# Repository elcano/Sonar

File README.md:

# Sonar
Range data from an array of ultra-sonic sensors

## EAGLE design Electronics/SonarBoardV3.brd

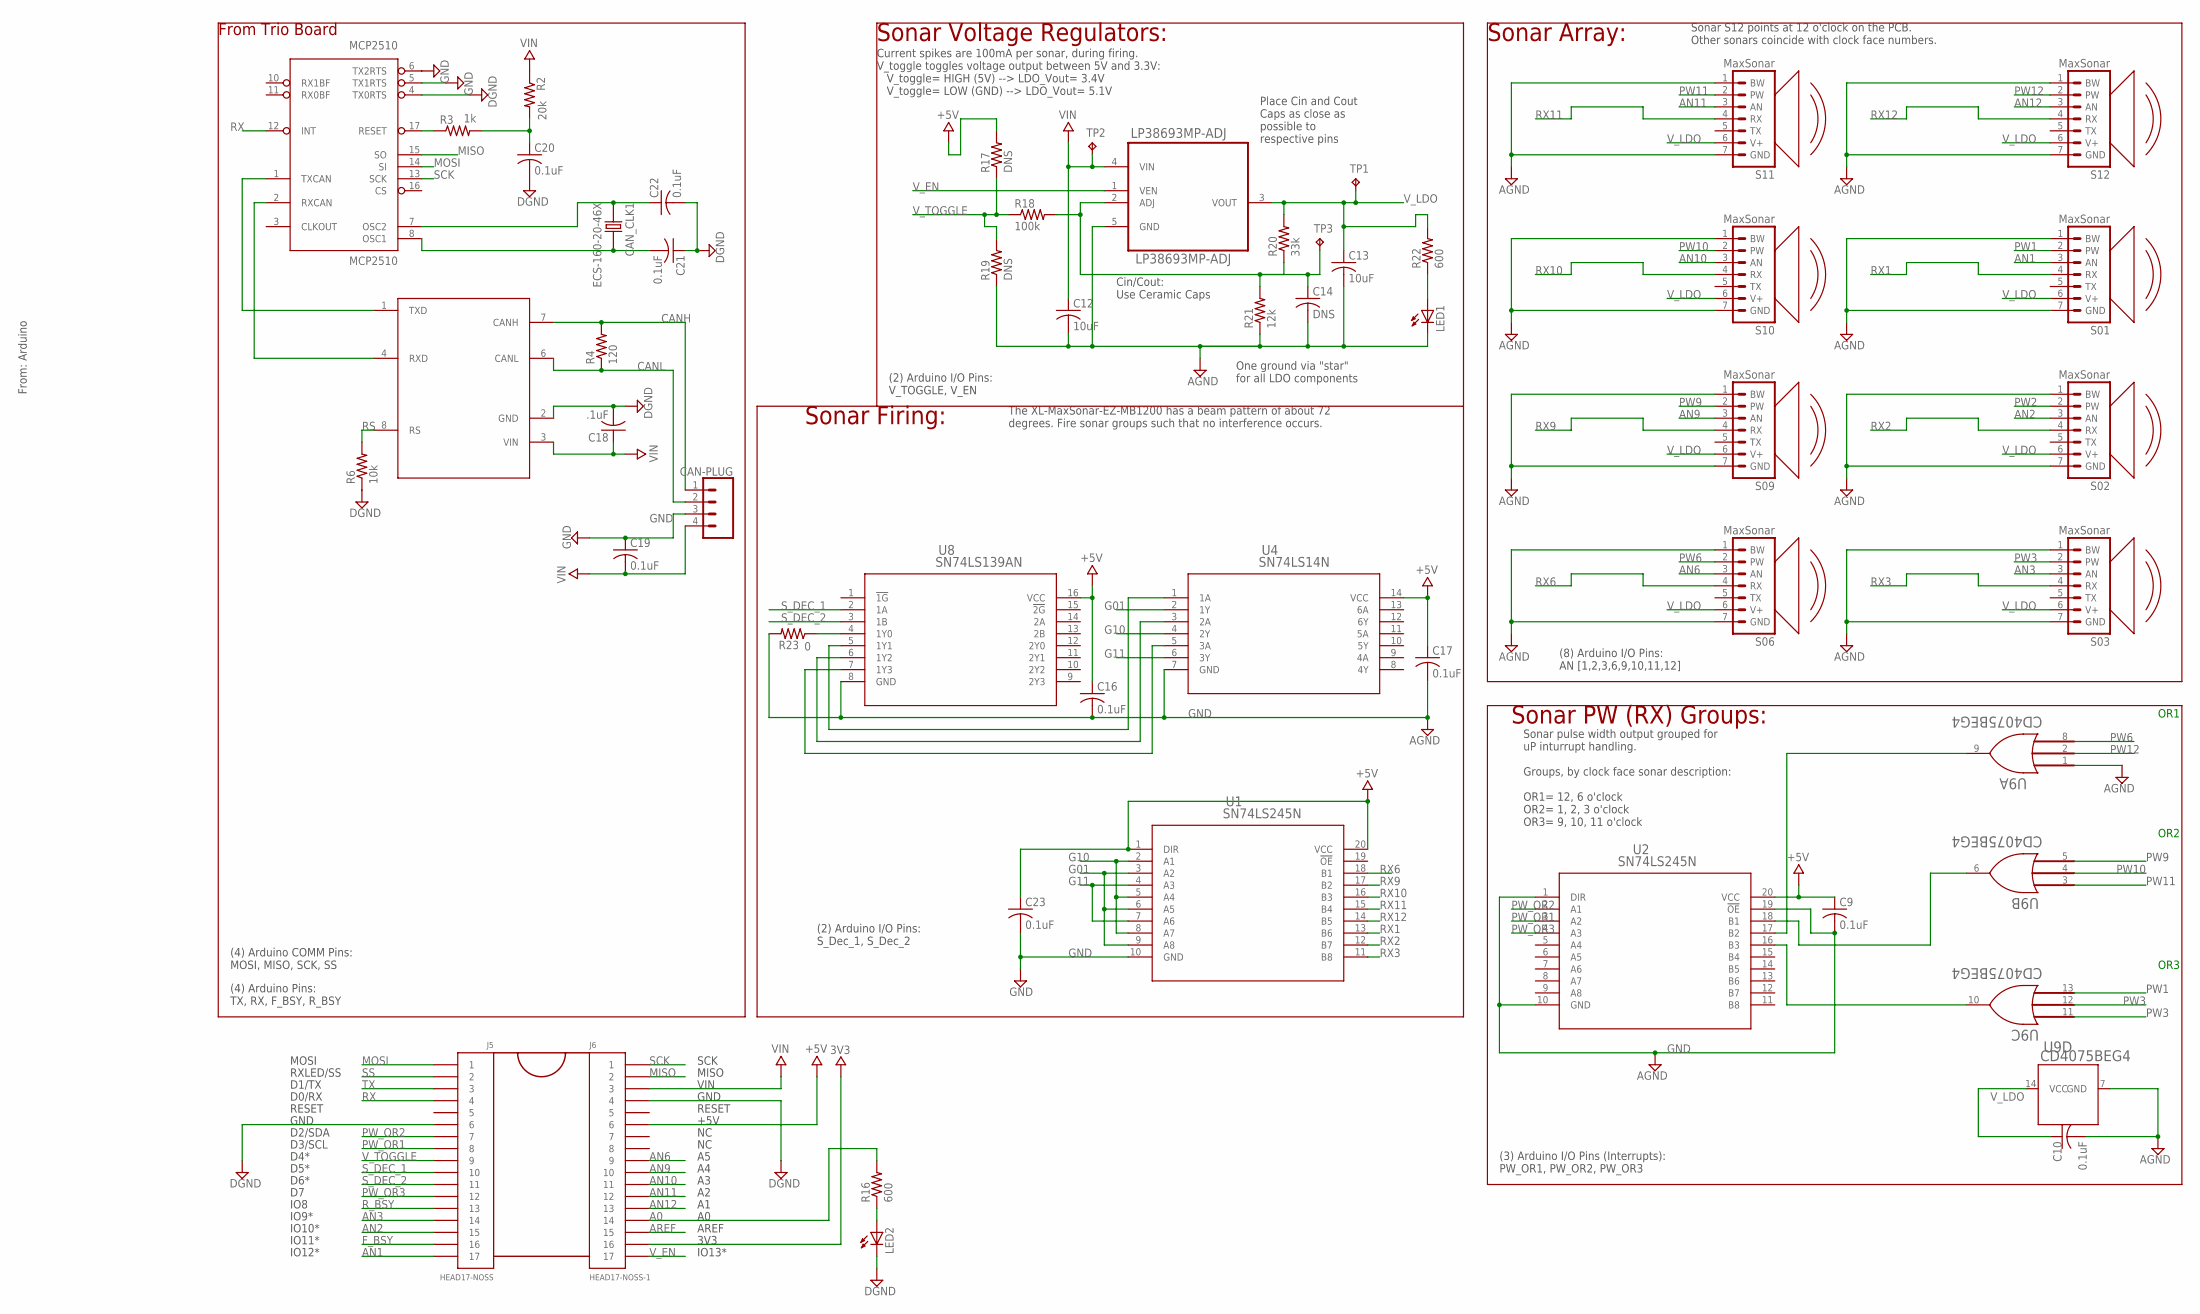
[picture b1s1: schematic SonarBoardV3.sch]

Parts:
C9, C10, C16, C17, C19, C20, C21, C22, C23: 0.1uF; C025-024X044
C12, C13: 10uF; C025-024X044
C14: DNS; C025-024X044
C18: .1uF; C025-024X044
CAN_CLK1: ECS-160-20-46X; XTAL_ECS-160-20-46X
J2: CAN-PLUG; SCREWTERMINAL-3.5MM-4
J5: HEAD17-NOSS
J6: HEAD17-NOSS-1
LED1, LED2: LED3MM
LP38693MP-ADJ: LP38693MP-ADJ; SOT150P696X180-5N
MCP2510: MCP2510; DIL18
MCP2551: MCP2551; DIL08
R2: 20k; 0207/9
R3: 1k; 0207/9
R4: 120; 0207/9
R6: 10k; 0207/9
R16, R22: 600; 0207/9
R17, R19: DNS; 0207/9
R18: 100k; 0207/9
R20: 33k; 0207/9
R21: 12k; 0207/9
R23: 0; 0207/9
S01, S02, S03, S06, S09, S10, S11, S12: MaxSonar; XL-MAXSONAR-PACKAGE
TP1, TP2, TP3: TPPAD1-17; P1-17
U1, U2: SN74LS245N; N20
U4: SN74LS14N; N14
U8: SN74LS139AN; N16
U9: CD4075BEG4; N14

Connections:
3V3: J6.16
+5V: C9.1, C16.1, C17.1, C23.1, J6.6, R17.2, U1.1 (DIR), U1.20 (VCC), U2.20 (VCC), U4.14 (VCC), U8.16 (VCC)
A0: J6.14, R16.2
AN1: J5.17, S01.3 (AN)
AN2: J5.15, S02.3 (AN)
AN3: J5.14, S03.3 (AN)
AN6: J6.9, S06.3 (AN)
AN9: J6.10, S09.3 (AN)
AN10: J6.11, S10.3 (AN)
AN11: J6.12, S11.3 (AN)
AN12: J6.13, S12.3 (AN)
AREF: J6.15
CANH: J2.1, MCP2551.7 (CANH), R4.2
CANL: J2.2, MCP2551.6 (CANL), R4.1
F_BSY: J5.16
G01: U1.3 (A2), U1.6 (A5), U1.9 (A8), U4.2 (1Y)
G10: U1.2 (A1), U1.5 (A4), U1.8 (A7), U4.4 (2Y)
G11: U1.4 (A3), U1.7 (A6), U4.6 (3Y)
GND: C9.2, C10.2, C12.2, C13.2, C14.2, C16.2, C17.2, C18.2, C19.1, C20.2, C21.1, C22.2, C23.2, J2.3, J5.6, J6.4, LED1.K (C), LED2.K (C), LP38693MP-ADJ.5 (GND), MCP2510.4 (TX0RTS), MCP2510.5 (TX1RTS), MCP2510.6 (TX2RTS), MCP2551.2 (GND), R6.1, R19.1, R21.1, R23.2, S01.1 (BW), S01.7 (GND), S02.1 (BW), S02.7 (GND), S03.1 (BW), S03.7 (GND), S06.1 (BW), S06.7 (GND), S09.1 (BW), S09.7 (GND), S10.1 (BW), S10.7 (GND), S11.1 (BW), S11.7 (GND), S12.1 (BW), S12.7 (GND), U1.10 (GND), U2.1 (DIR), U2.10 (GND), U2.19 (!OE), U4.7 (GND), U8.8 (GND), U9.7 (GND)
MISO: J6.2, MCP2510.15 (SO)
MOSI: J5.1, MCP2510.14 (SI)
unnamed: U4.5 (3A), U8.7 (1Y3)
unnamed: LED2.A, R16.1
unnamed: U2.16 (B3), U9.10 (J)
unnamed: C21.2, CAN_CLK1.2, MCP2510.8 (OSC1)
unnamed: U4.3 (2A), U8.6 (1Y2)
unnamed: LED1.A, R22.1
unnamed: U4.1 (1A), U8.5 (1Y1)
unnamed: C22.1, CAN_CLK1.1, MCP2510.7 (OSC2)
unnamed: MCP2510.2 (RXCAN), MCP2551.4 (RXD)
unnamed: MCP2510.1 (TXCAN), MCP2551.1 (TXD)
unnamed: MCP2510.17 (RESET), R3.1
unnamed: C20.1, R2.2, R3.2
unnamed: R23.1, U8.4 (1Y0)
unnamed: U2.17 (B2), U9.9 (J)
unnamed: U2.18 (B1), U9.6 (J)
PW1: S01.2 (PW)
PW2: S02.2 (PW)
PW3: S03.2 (PW)
PW6: S06.2 (PW)
PW9: S09.2 (PW)
PW10: S10.2 (PW)
PW11: S11.2 (PW)
PW12: S12.2 (PW)
PW_OR1: J5.8, U2.3 (A2)
PW_OR2: J5.7, U2.2 (A1)
PW_OR3: J5.12, U2.4 (A3)
RS: MCP2551.8 (RS), R6.2
RX: J5.4, MCP2510.12 (INT)
RX1: S01.4 (RX), U1.13 (B6)
RX2: S02.4 (RX), U1.12 (B7)
RX3: S03.4 (RX), U1.11 (B8)
RX6: S06.4 (RX), U1.18 (B1)
RX9: S09.4 (RX), U1.17 (B2)
RX10: S10.4 (RX), U1.16 (B3)
RX11: S11.4 (RX), U1.15 (B4)
RX12: S12.4 (RX), U1.14 (B5)
R_BSY: J5.13
SCK: J6.1, MCP2510.13 (SCK)
SS: J5.2
S_DEC_1: J5.10, U8.2 (1A)
S_DEC_2: J5.11, U8.3 (1B)
TX: J5.3
VIN: C12.1, C18.1, C19.2, J2.4, J6.3, LP38693MP-ADJ.4 (VIN), MCP2551.3 (VIN), R2.1, TP2.TP
V_ADJ: C14.1, LP38693MP-ADJ.2 (ADJ), R18.2, R20.1, R21.2, TP3.TP
V_EN: J6.17, LP38693MP-ADJ.1 (VEN)
V_LDO: C10.1, C13.1, LP38693MP-ADJ.3 (VOUT), R20.2, R22.2, S01.6 (V+), S02.6 (V+), S03.6 (V+), S06.6 (V+), S09.6 (V+), S10.6 (V+), S11.6 (V+), S12.6 (V+), TP1.TP, U9.14 (VCC)
V_TOGGLE: J5.9, R17.1, R18.1, R19.2

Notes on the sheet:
Sonar S12 points at 12 o'clock on the PCB. Other sonars coincide with clock face numbers.
From Trio Board
The XL-MaxSonar-EZ-MB1200 has a beam pattern of about 72 degrees. Fire sonar groups such that no interference occurs.
Sonar Voltage Regulators:
Place Cin and Cout Caps as close as possible to respective pins
One ground via "star" for all LDO components
Current spikes are 100mA per sonar, during firing. V_toggle toggles voltage output between 5V and 3.3V: V_toggle= HIGH (5V) --> LDO_Vout= 3.4V V_toggle= LOW (GND) --> LDO_Vout= 5.1V
Cin/Cout: Use Ceramic Caps
From: Arduino
Sonar Firing:
Sonar Array:
(2) Arduino I/O Pins: S_Dec_1, S_Dec_2
(2) Arduino I/O Pins: V_TOGGLE, V_EN
(8) Arduino I/O Pins: AN [1,2,3,6,9,10,11,12]
Sonar PW (RX) Groups:
Sonar pulse width output grouped for uP inturrupt handling. Groups, by clock face sonar description: OR1= 12, 6 o'clock OR2= 1, 2, 3 o'clock OR3= 9, 10, 11 o'clock
(3) Arduino I/O Pins (Interrupts): PW_OR1, PW_OR2, PW_OR3
(4) Arduino COMM Pins: MOSI, MISO, SCK, SS
(4) Arduino Pins: TX, RX, F_BSY, R_BSY
MOSI
RXLED/SS
D1/TX
D0/RX
RESET
GND
D2/SDA
D3/SCL
D4*
D5*
IO8
D6*
IO9*
IO10*
IO11*
IO12*
SCK
MISO
VIN
+5V
AREF

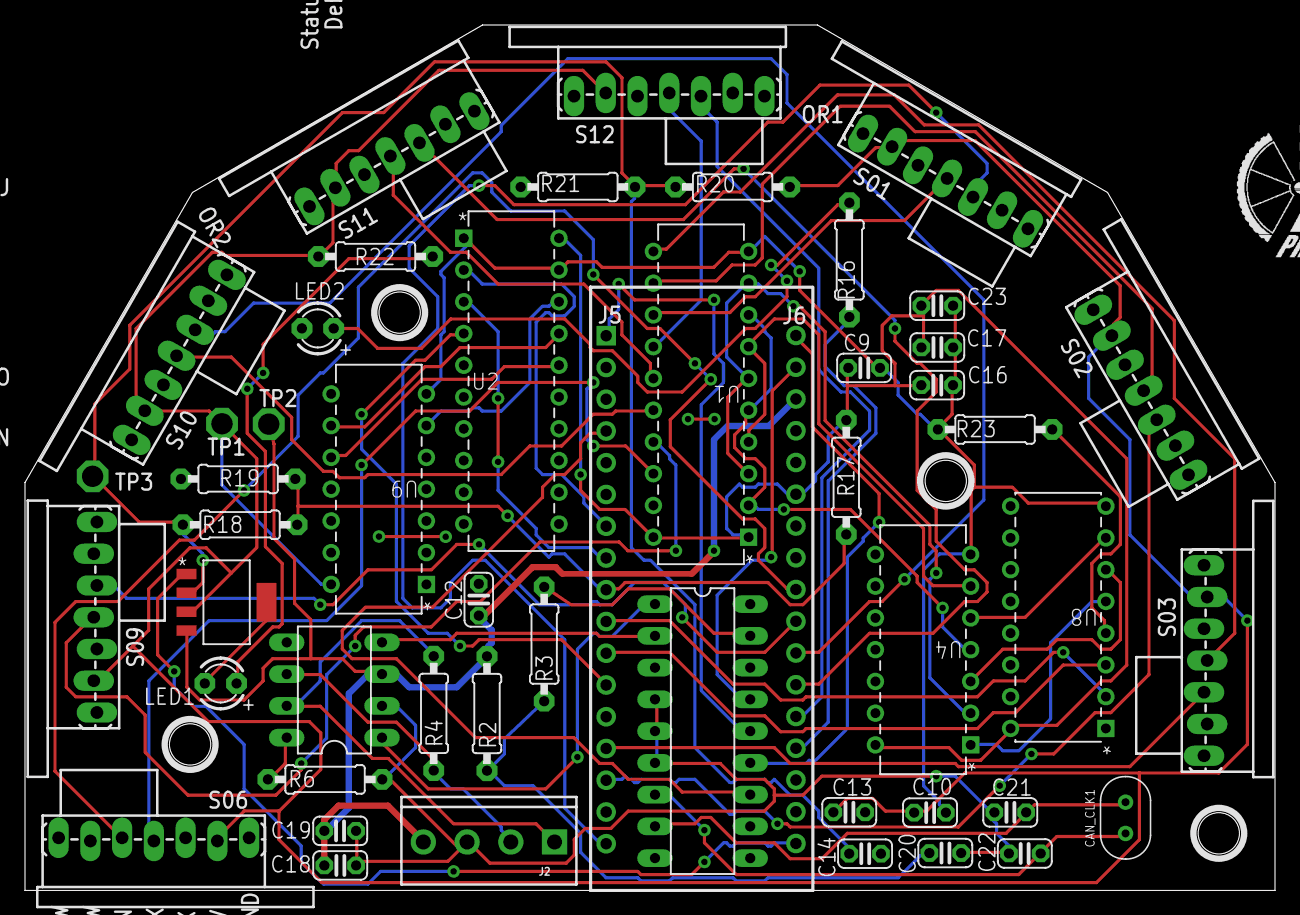
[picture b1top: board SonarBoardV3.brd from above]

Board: 2 copper layers, 100.0 x 69.2 mm, 54 parts (0 on the bottom side), 54 nets.

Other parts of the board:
U$15, U$16, U$17, U$18: STAND-OFF

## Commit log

2019-06-20 Renamed Sonar without ElcanoC5
2019-06-20 Moved to electronics directory
2019-06-20 Added relevant documentation
2019-06-20 Added License and ReadMe
2019-12-10 CAN design
    Michell Dean's design for moving from Version 3 (communicate on differential SPI) to Version 3 (CAN bus communications). Version 3 board has not been built.

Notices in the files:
parts and their libraries:
SparkFun-Electromechanical: Licensing: Creative Commons ShareAlike 4.0 International - https://creativecommons.org/licenses/by-sa/4.0
